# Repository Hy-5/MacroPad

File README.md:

# MacroPad
 MacroPad PCB Design - WIP

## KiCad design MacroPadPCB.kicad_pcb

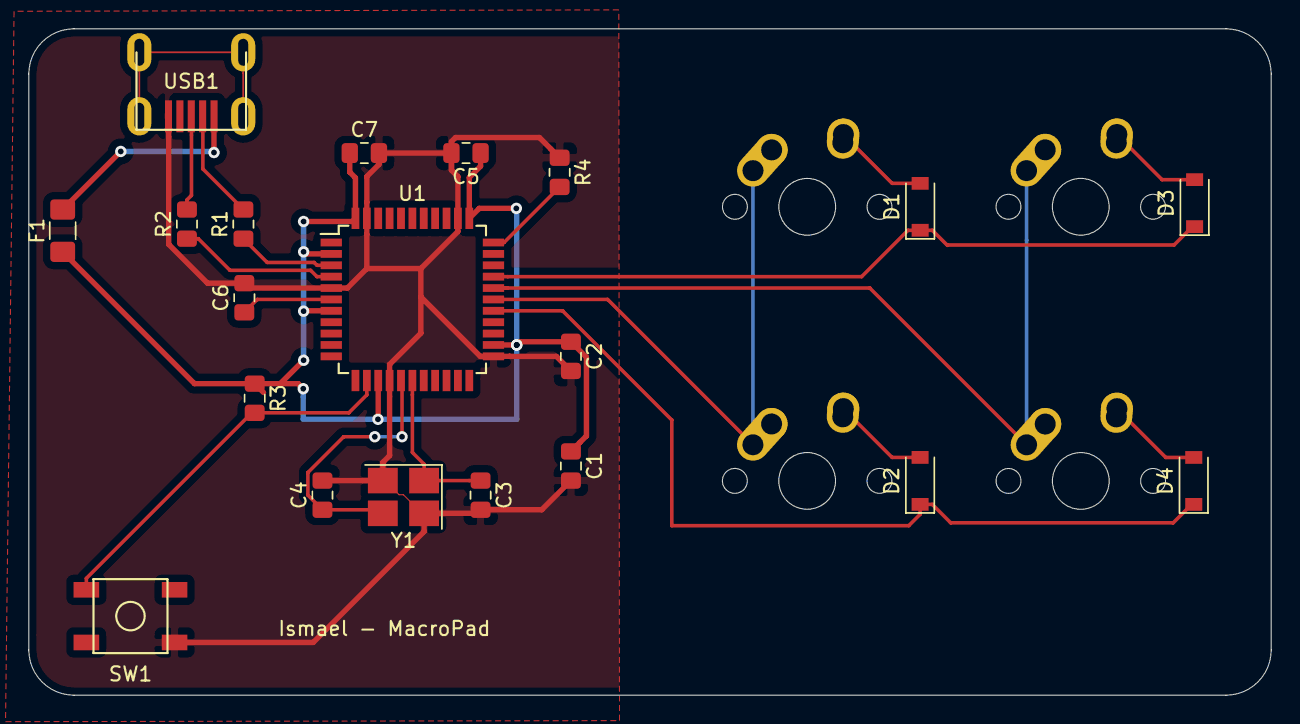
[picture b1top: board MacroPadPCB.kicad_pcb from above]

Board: 2 copper layers, 87.3 x 46.8 mm, 24 parts (0 on the bottom side), 20 nets.

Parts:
C1, C2, C5: 0.1uF; C_0805_2012Metric_Pad1.15x1.40mm_HandSolder
C3, C4: 22pF; C_0805_2012Metric_Pad1.15x1.40mm_HandSolder
C6: 1uF; C_0805_2012Metric_Pad1.15x1.40mm_HandSolder
C7: 10uF; C_0805_2012Metric_Pad1.15x1.40mm_HandSolder
D1, D2, D3, D4: D_Small; D_SOD-123
F1: 500mA; Fuse_1206_3216Metric_Pad1.42x1.75mm_HandSolder
MX1, MX2, MX3, MX4: MX-NoLED; MX-1U-NoLED
R1, R2: 22; R_0805_2012Metric_Pad1.15x1.40mm_HandSolder
R3, R4: 10k; R_0805_2012Metric_Pad1.15x1.40mm_HandSolder
SW1: SW_Push; SKQG-1155865
U1: ATmega32U4-AU; TQFP-44_10x10mm_P0.8mm
USB1: Molex-0548190589
Y1: 16MHz; Crystal_SMD_3225-4Pin_3.2x2.5mm_HandSoldering

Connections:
+5V: C1.1, C2.1, C5.1, C7.1, F1.1, R3.1, U1.2, U1.7, U1.14, U1.24, U1.34, U1.44
COL0: MX1.1, MX2.1, U1.28
COL1: MX3.1, MX4.1, U1.29
D+: R2.2, USB1.3
D-: R1.2, USB1.4
GND: C1.2, C2.2, C3.2, C4.2, C5.2, C6.2, C7.2, R4.1, SW1.1, U1.5, U1.15, U1.23, U1.35, U1.43, USB1.1, Y1.2, Y1.4
unnamed: C3.1, U1.17, Y1.1
unnamed: C4.1, U1.16, Y1.3
unnamed: C6.1, U1.6
unnamed: D1.2, MX1.2
unnamed: D2.2, MX2.2
unnamed: D3.2, MX3.2
unnamed: D4.2, MX4.2
unnamed: R1.1, U1.3
unnamed: R2.1, U1.4
unnamed: R3.2, SW1.2, U1.13
unnamed: R4.2, U1.33
ROW0: D1.1, D3.1, U1.30
ROW1: D2.1, D4.1, U1.27
VCC: F1.2, USB1.5

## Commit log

2022-07-13 Added basics components
2023-10-11 Project Initialization
2023-10-12 Add submodules
2023-10-12 Setting up environment
2023-10-12 Schematic complete
2023-10-14 PCB build and routing
2023-10-14 Ground filling done - Bug fixing WIP
